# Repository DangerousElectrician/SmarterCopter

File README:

better brains for a syma 107 toy helicopter

Stuff to fix:
Holes are spaced back to front. Hole sizes are fine
U2 grounding pad covered by soldermask
Mousebites need to be sanded flat

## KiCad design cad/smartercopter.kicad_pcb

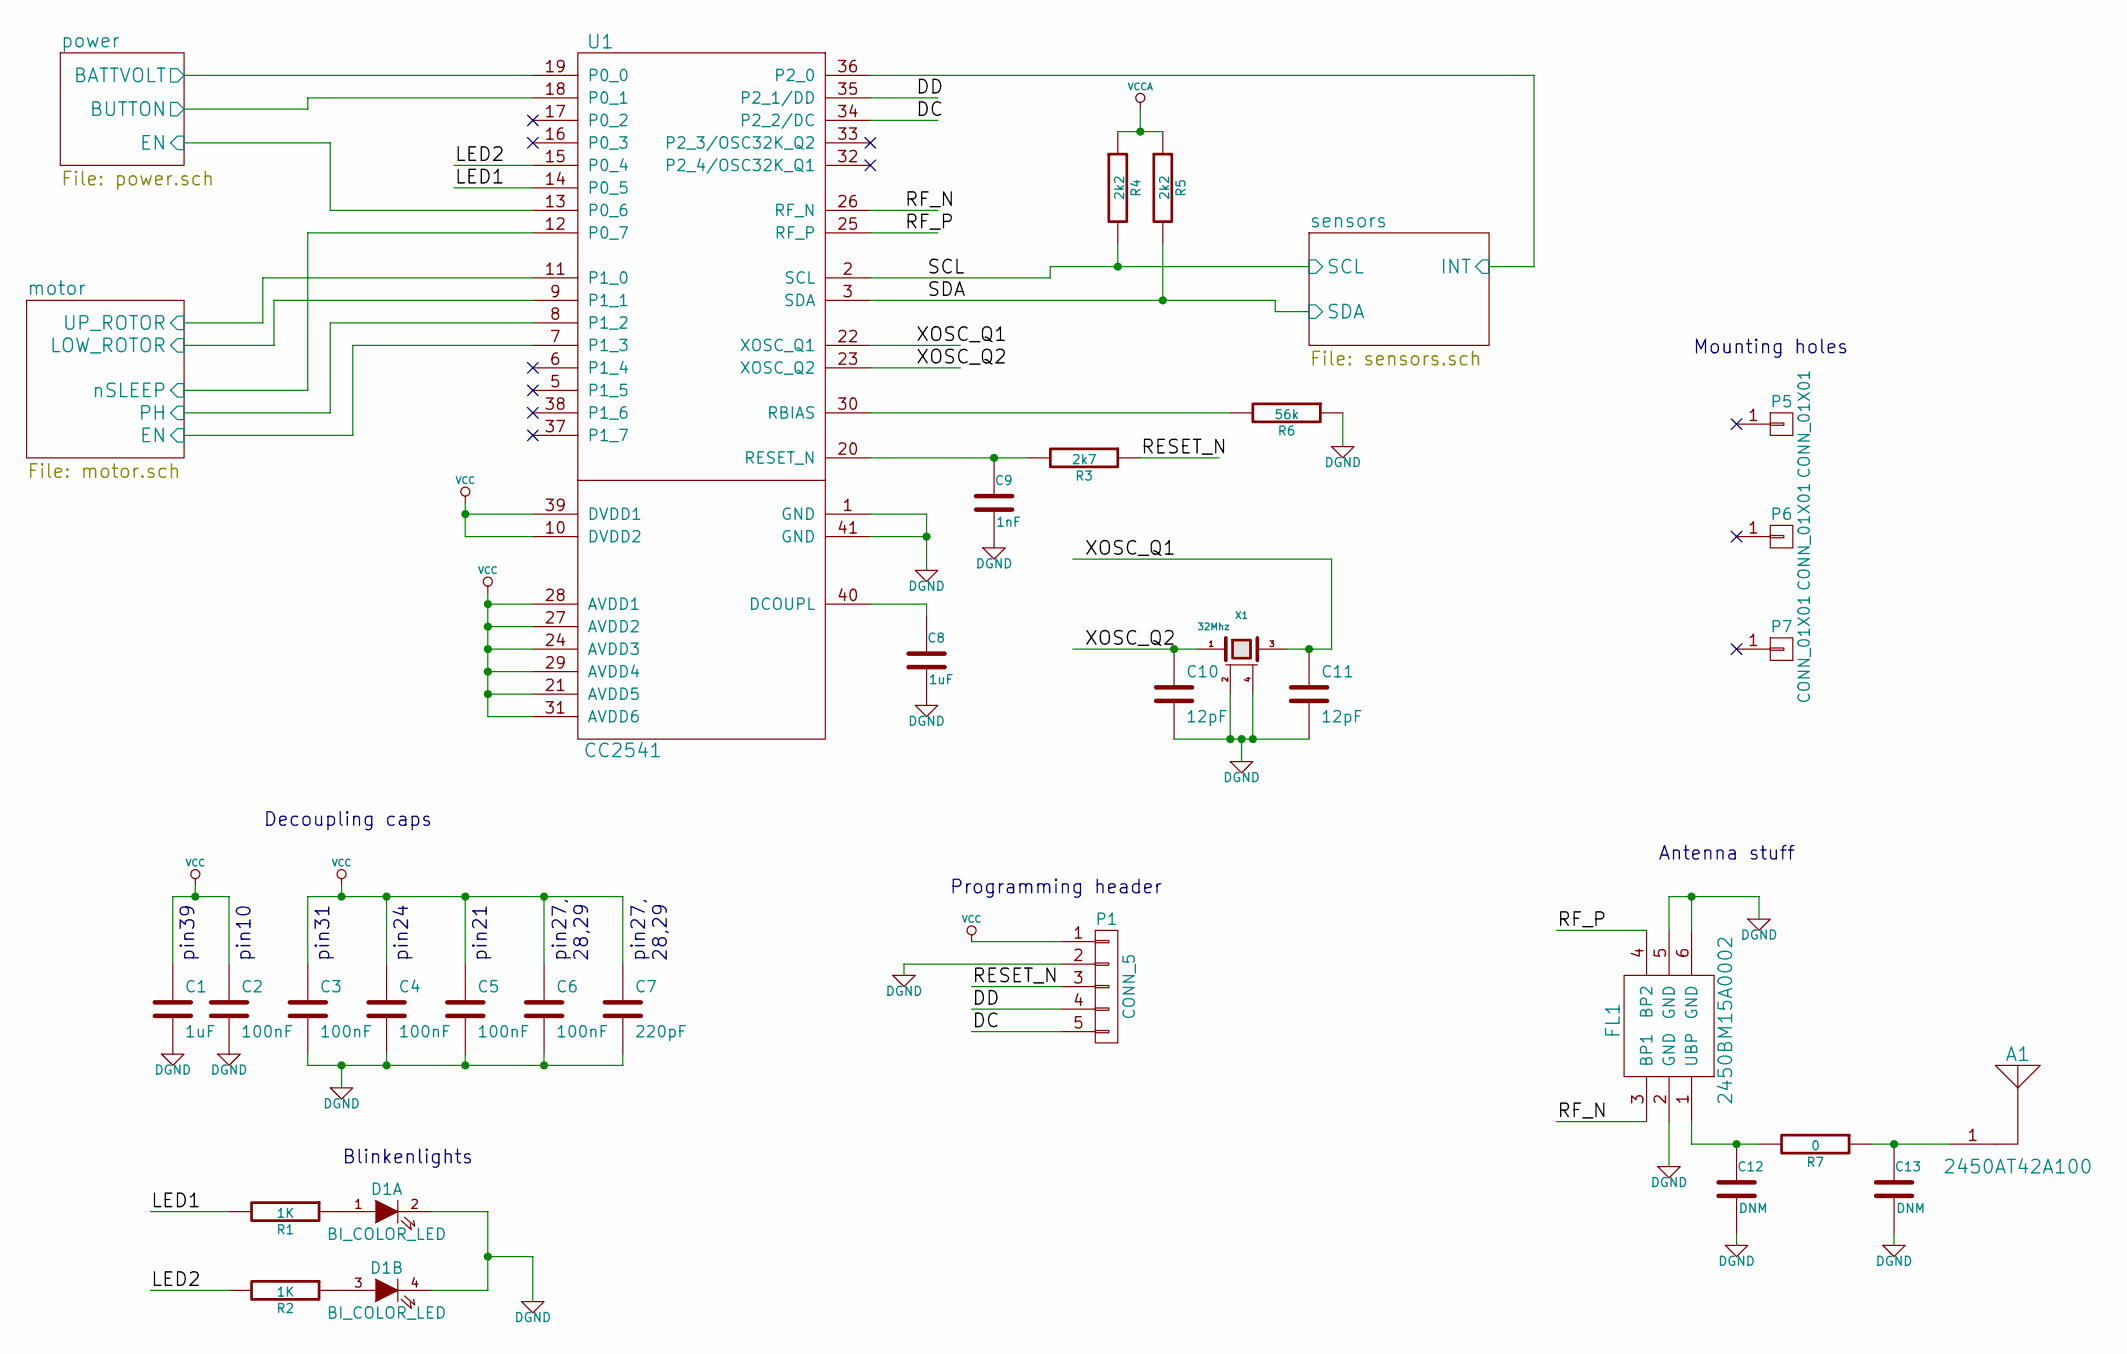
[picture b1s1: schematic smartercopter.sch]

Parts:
A1: 2450AT42A100; MPN 2450AT42A100
C1: 1uF; C_0402; MPN GRM155R60J105KE19D
C2: 100nF; C_0402; MPN LMK105BJ104KV-F
C3, C4, C5, C6: 100nF; C_0402
C7: 220pF; C_0402; MPN CC0402KRX7R9BB221
C8: 1uF; C_0402
C9: 1nF; C_0402; MPN GRM155R71H102KA01D
C10: 12pF; C_0201; MPN 02013A120JAT2A
C11: 12pF; C_0201
C12, C13: DNM; C_0402
D1: BI_COLOR_LED; APTB1612ESGC-F01; MPN APTB1612ESGC-F01
FL1: 2450BM15A0002; MPN 2450BM15A0002
P1: CONN_5; pin_array_1x05
P5, P6, P7: CONN_01X01; MountingHole_3mm
R1: 1K; R_0402; MPN 1-1622826-8
R2: 1K; R_0402
R3: 2k7; R_0402; MPN RMCF0402JT2K70
R4, R5: 2k2; R_0402
R6: 56k; R_0402; MPN MCR01MRTF5602
R7: 0; R_0402
U1: CC2541; VQFN-40; MPN CC2541F256RHAR
X1: 32Mhz; 4-SMD; MPN FA-128 32.0000MF20X-K3

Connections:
/DC: P1.5, U1.34 (P2_2/DC)
/DD: P1.4, U1.35 (P2_1/DD)
/LED1: R1.2, U1.14 (P0_5)
/LED2: R2.2, U1.15 (P0_4)
/RESET_N: P1.3, R3.1
/RF_N: FL1.3 (BP1), U1.26 (RF_N)
/RF_P: FL1.4 (BP2), U1.25 (RF_P)
/XOSC_Q1: C11.1, U1.22 (XOSC_Q1), X1.3
/XOSC_Q2: C10.1, U1.23 (XOSC_Q2), X1.1
/motor/EN: U1.7 (P1_3); also elsewhere on the board
/motor/LOW_ROTOR: U1.9 (P1_1); also elsewhere on the board
/motor/PH: U1.8 (P1_2); also elsewhere on the board
/motor/UP_ROTOR: U1.11 (P1_0); also elsewhere on the board
/motor/nSLEEP: U1.12 (P0_7); also elsewhere on the board
/power/BATTVOLT: U1.19 (P0_0); also elsewhere on the board
/power/BUTTON: U1.18 (P0_1); also elsewhere on the board
/power/EN: U1.13 (P0_6); also elsewhere on the board
/sensors/INT: U1.36 (P2_0); also elsewhere on the board
/sensors/SCL: R4.2, U1.2 (SCL); also elsewhere on the board
/sensors/SDA: R5.2, U1.3 (SDA); also elsewhere on the board
DGND: C1.2, C2.2, C3.2, C4.2, C5.2, C6.2, C7.2, C8.2, C9.2, C10.2, C11.2, C12.2, C13.2, D1.2 (K), D1.4 (K), FL1.2 (GND), FL1.5 (GND), FL1.6 (GND), P1.2, R6.1, U1.1 (GND), U1.41 (GND), X1.2 (GND), X1.4 (GND); also elsewhere on the board
unnamed: A1.1, C13.1, R7.1
unnamed: C8.1, U1.40 (DCOUPL)
unnamed: C9.1, R3.2, U1.20 (RESET_N)
unnamed: C12.1, FL1.1 (UBP), R7.2
unnamed: D1.1 (A), R1.1
unnamed: D1.3 (A), R2.1
unnamed: R6.2, U1.30 (RBIAS)
VCC: C1.1, C2.1, C3.1, C4.1, C5.1, C6.1, C7.1, P1.1, U1.10 (DVDD2), U1.21 (AVDD5), U1.24 (AVDD3), U1.27 (AVDD2), U1.28 (AVDD1), U1.29 (AVDD4), U1.31 (AVDD6), U1.39 (DVDD1); also elsewhere on the board
VCCA: R4.1, R5.1; also elsewhere on the board

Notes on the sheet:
pin39
pin10
pin31
pin24
pin21
pin27, 28,29
Blinkenlights
Antenna stuff
Programming header
Decoupling caps
Mounting holes

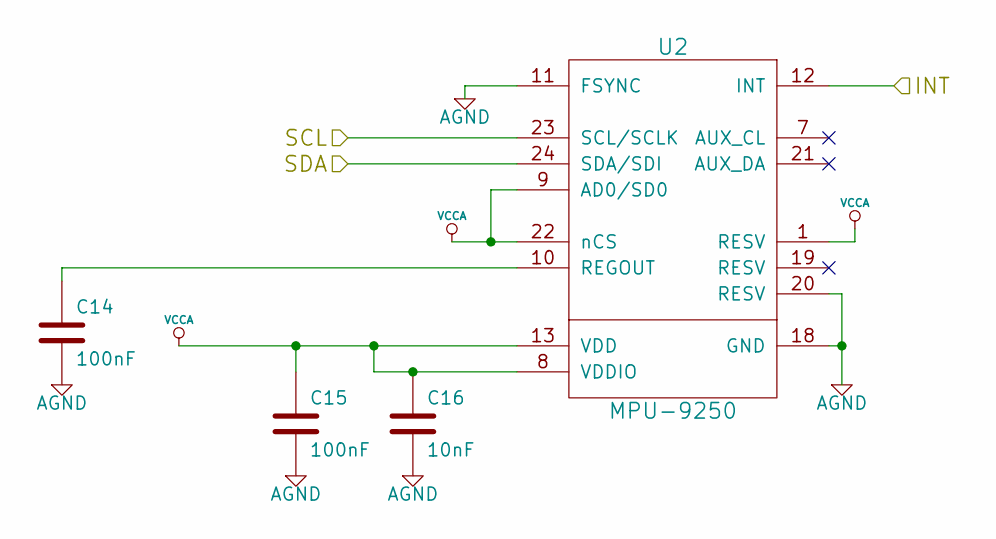
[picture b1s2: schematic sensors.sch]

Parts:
C14, C15: 100nF; C_0402
C16: 10nF; C_0402; MPN GRM155R71E103KA01D
U2: MPU-9250; QFN-28-1EP; MPN MPU-9250

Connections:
/sensors/INT: U2.12 (INT); also elsewhere on the board
/sensors/SCL: U2.23 (SCL/SCLK); also elsewhere on the board
/sensors/SDA: U2.24 (SDA/SDI); also elsewhere on the board
AGND: C14.2, C15.2, C16.2, U2.11 (FSYNC), U2.18 (GND), U2.20 (RESV); also elsewhere on the board
unnamed: C14.1, U2.10 (REGOUT)
VCCA: C15.1, C16.1, U2.1 (RESV), U2.8 (VDDIO), U2.9 (AD0/SD0), U2.13 (VDD), U2.22 (nCS); also elsewhere on the board

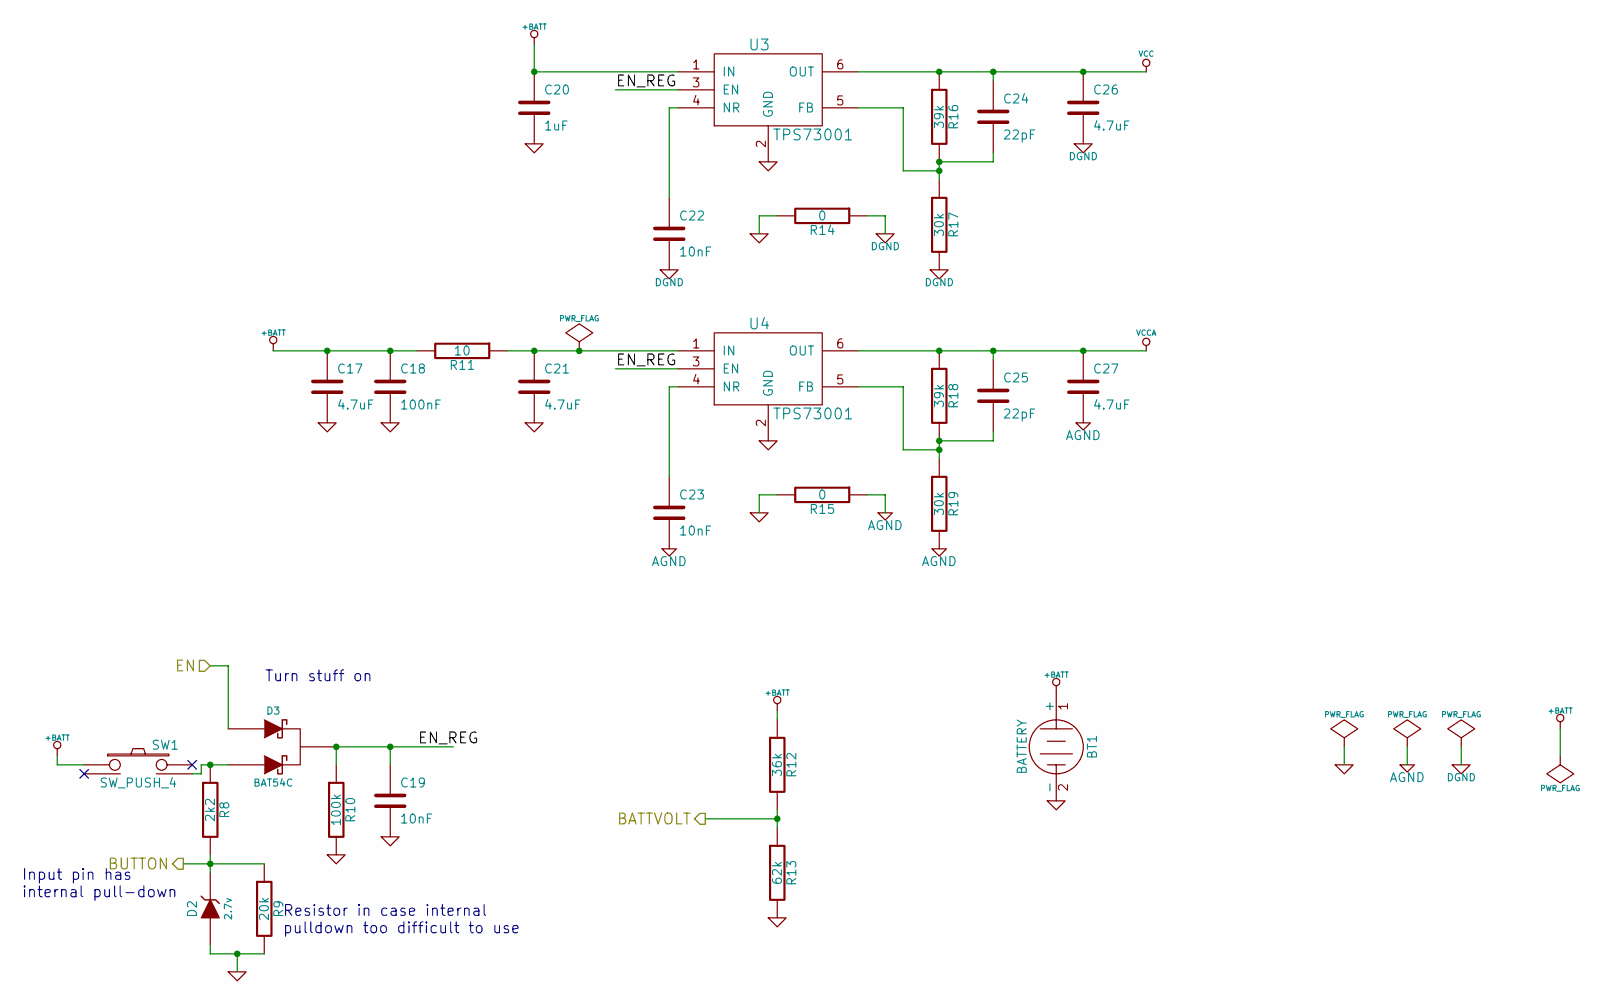
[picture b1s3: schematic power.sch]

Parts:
BT1: BATTERY; Pin_Header_Straight_1x02
C17, C21, C27: 4.7uF; C_0603
C18: 100nF; C_0402
C19, C22, C23: 10nF; C_0402
C20: 1uF; C_0402
C24: 22pF; C_0402; MPN CL05C220JB5NNNC
C25: 22pF; C_0402
C26: 4.7uF; C_0603; MPN CL10B475KQ8NQNC
D2: 2.7v; SOD-323; MPN MM3Z2V7T1G
D3: BAT54C; Diode_SOT23
R8: 2k2; R_0402; MPN RMCF0402JT2K20
R9: 20k; R_0402; MPN MCR01MRTF2002
R10: 100k; R_0402; MPN MCR01MRTF1003
R11: 10; R_0402; MPN MCR01MRTF10R0
R12: 36k; R_0402; MPN MCR01MRTF3602
R13: 62k; R_0402; MPN MCR01MRTJ623
R14: 0; R_0402; MPN RC1005J000CS
R15: 0; R_0402
R16: 39k; R_0402; MPN RC1005J393CS
R17: 30k; R_0402; MPN RC1005J303CS
R18: 39k; R_0402
R19: 30k; R_0402
SW1: SW_PUSH_4; PTS840GMSMTRLFS; MPN PTS840 GM SMTR LFS
U3: TPS73001; SOT-23-6; MPN TPS73001DBVR
U4: TPS73001; SOT-23-6

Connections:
+BATT: BT1.1 (+), C17.1, C18.1, C20.1, R11.2, R12.1, SW1.1, U3.1 (IN); also elsewhere on the board
/power/BATTVOLT: R12.2, R13.1; also elsewhere on the board
/power/BUTTON: D2.2 (K), R8.2, R9.1; also elsewhere on the board
/power/EN: D3.1; also elsewhere on the board
/power/EN_REG: C19.1, D3.3, R10.1, U3.3 (EN), U4.3 (EN)
AGND: C23.2, C27.2, R15.1, R19.2; also elsewhere on the board
DGND: C22.2, C26.2, R14.1, R17.2; also elsewhere on the board
GND: BT1.2 (-), C17.2, C18.2, C19.2, C20.2, C21.2, D2.1 (A), R9.2, R10.2, R13.2, R14.2, R15.2, U3.2 (GND), U4.2 (GND); also elsewhere on the board
unnamed: C21.1, R11.1, U4.1 (IN)
unnamed: C22.1, U3.4 (NR)
unnamed: C23.1, U4.4 (NR)
unnamed: C24.2, R16.2, R17.1, U3.5 (FB)
unnamed: C25.2, R18.2, R19.1, U4.5 (FB)
unnamed: D3.2, R8.1, SW1.4
VCC: C24.1, C26.1, R16.1, U3.6 (OUT); also elsewhere on the board
VCCA: C25.1, C27.1, R18.1, U4.6 (OUT); also elsewhere on the board

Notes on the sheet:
Input pin has internal pull-down
Resistor in case internal pulldown too difficult to use
Turn stuff on

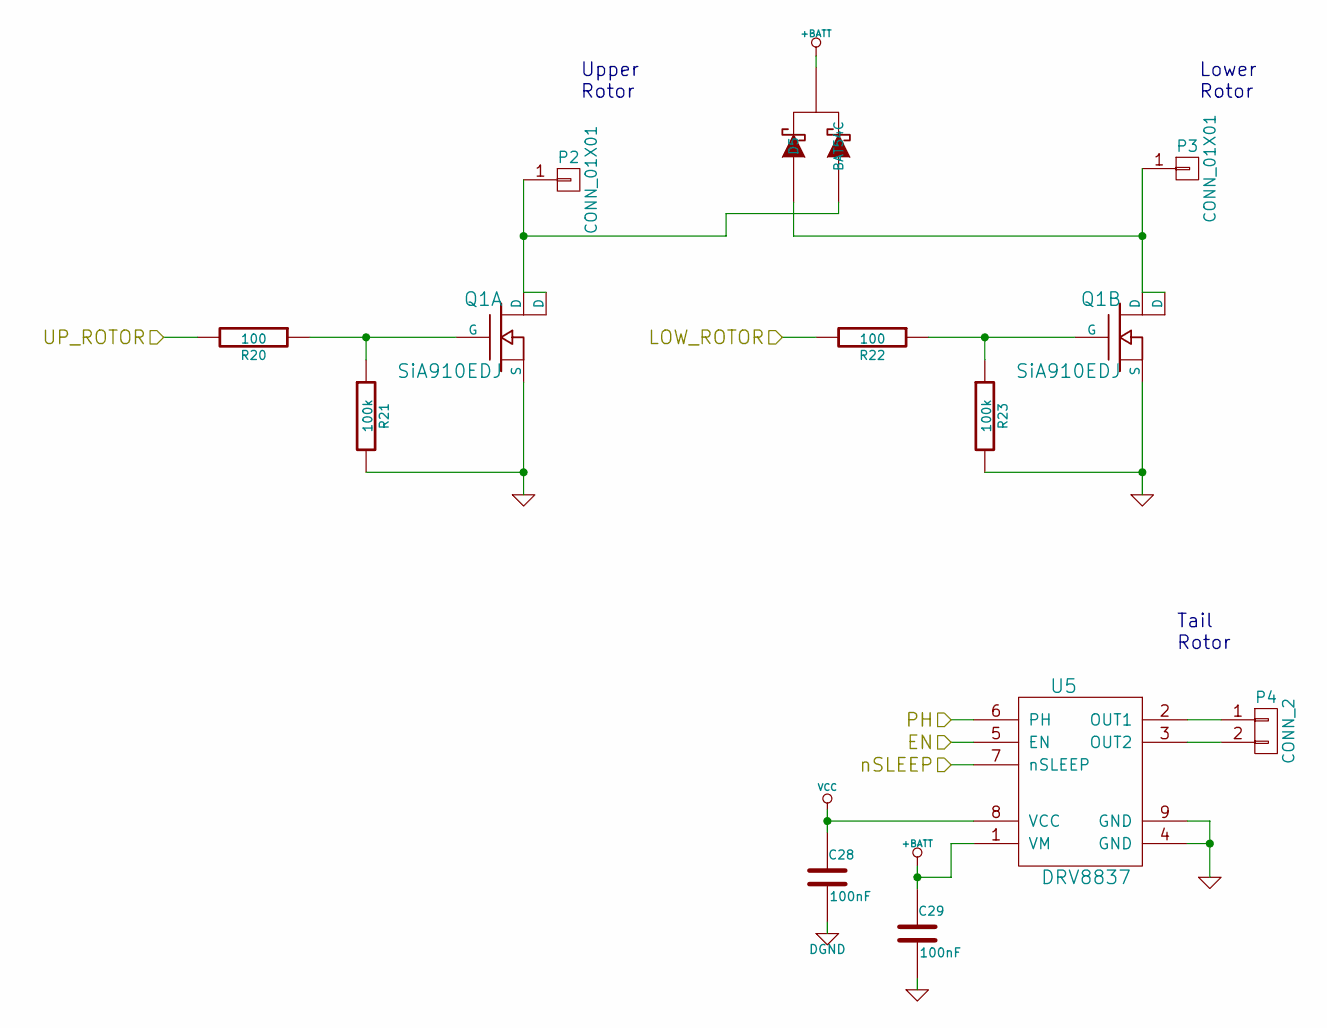
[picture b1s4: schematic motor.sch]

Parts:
C28, C29: 100nF; C_0402
D5: BAT54C; Diode_SOT23; MPN BAT54C
P2, P3: CONN_01X01; Pin_Header_Straight_1x01
P4: CONN_2; Pin_Header_Straight_1x02
Q1: SiA910EDJ; SC-70-6L; MPN SIA910EDJ-T1-GE3
R20: 100; R_0402; MPN MCR01MRTF1000
R21, R23: 100k; R_0402
R22: 100; R_0402
U5: DRV8837; WSON-8-1EP; MPN DRV8837DSGR

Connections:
+BATT: C29.1, D5.3, U5.1 (VM); also elsewhere on the board
/motor/EN: U5.5 (EN); also elsewhere on the board
/motor/LOW_ROTOR: R22.2; also elsewhere on the board
/motor/PH: U5.6 (PH); also elsewhere on the board
/motor/UP_ROTOR: R20.2; also elsewhere on the board
/motor/nSLEEP: U5.7 (nSLEEP); also elsewhere on the board
DGND: C28.2; also elsewhere on the board
GND: C29.2, Q1.1 (S), Q1.4 (S), R21.2, R23.2, U5.4 (GND), U5.9 (GND); also elsewhere on the board
unnamed: D5.1, P3.1, Q1.3 (D), Q1.D2 (D)
unnamed: D5.2, P2.1, Q1.6 (D), Q1.D1 (D)
unnamed: P4.1, U5.2 (OUT1)
unnamed: P4.2, U5.3 (OUT2)
unnamed: Q1.2 (G), R20.1, R21.1
unnamed: Q1.5 (G), R22.1, R23.1
VCC: C28.1, U5.8 (VCC); also elsewhere on the board

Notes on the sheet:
Upper Rotor
Lower Rotor
Tail Rotor

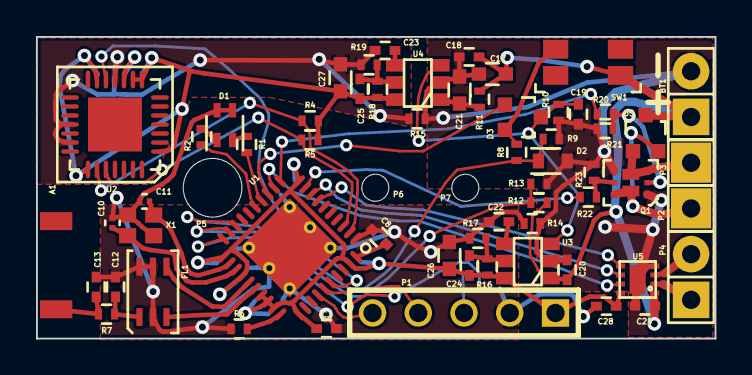
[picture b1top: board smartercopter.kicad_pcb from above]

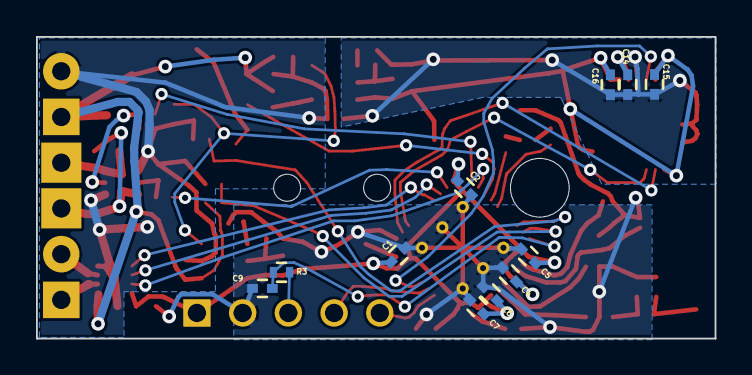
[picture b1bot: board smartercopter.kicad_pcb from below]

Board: 2 copper layers, 37.7 x 16.8 mm, 74 parts (11 on the bottom side), 47 nets.

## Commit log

2014-12-07 init commit
2014-12-08 added more sensor and processor considerations
2014-12-09 more details to microprocessor selection
2014-12-09 more stuff about sensors
2014-12-09 considering another sensor
2014-12-10 added requirements at top and a bit more information on sensors and motor drive
2014-12-10 more stuff on todo list
2014-12-10 figured out power requirements of CC2541 and MPU9250
2014-12-10 added some voltage regulator details
2014-12-11 added soft power switch pins to pin list
2014-12-11 added stuff about flyback diodes
2014-12-12 added soft power switch information
2014-12-14 changed voltage regulator
2014-12-17 schematics and datasheets
2014-12-17 added values to crystal load caps
2014-12-17 passed erc
2014-12-17 cleaned up a bit
2014-12-17 added .gitignore
2014-12-17 stuff
2014-12-18 something required to generate a BOM. not quite sure what it does
2014-12-18 auto generated xml file that does something
2014-12-18 did stuff here, not exactly sure what
2014-12-18 added more stuff to bom
2014-12-18 selecting parts for the little passives
2014-12-19 whole bunch of stuff
2014-12-19 more stuff
2014-12-20 reshuffled libraries
2014-12-20 updated libraries on .net file
2014-12-20 updated BOM
2014-12-21 crystal datasheet
2014-12-21 pcb file
2014-12-21 added more footprint stuff
2014-12-22 bunch more footprints assigned
2014-12-22 everything has a footprint
2014-12-22 all components spread out on sheet
2014-12-22 found out decoupling caps are not connected in the net
2014-12-23 arranged stuff into smaller groups
2014-12-23 components packed closer
2014-12-23 board outline
2014-12-23 added board outline
2014-12-23 made motor pads single to save space
2014-12-24 packed most of the components on to board
2014-12-24 everything on board
2014-12-24 routing first, then placing
2014-12-24 routed voltage regulators
2014-12-25 routed some stuff
2014-12-26 stuff on board with a bit of routing
2014-12-26 stuff on board
2014-12-27 progress check in
2014-12-27 freerouting stuff
2014-12-28 more routing
2014-12-30 components placed again
2014-12-30 freerouting files
2015-01-01 routing almost done
2015-01-01 everything routed
2015-01-02 everything routed for sure this time
2015-01-02 no drc errors
2015-01-02 added some ground planes
2015-01-04 added readme
2015-01-05 more power planes
2015-01-11 double checking qfn-40 footprint
2015-01-15 changed cc2451 footprint center pad
2015-01-17 all routed
2015-01-18 added ground planes
2015-01-18 changed ground plane clearences
2015-01-23 example script from the manual
2015-02-02 don't write anything
2015-02-05 figured out how to change text dimensions from script
2015-02-05 shrank all component references
2015-02-05 renamed script
2015-02-05 shrank all the silkscreen references
2015-02-05 git wants me to delete this in a weird way
2015-02-06 moved references around
2015-02-06 renamed files
2015-02-07 increased soldermask clearance from 0 to 3mil
2015-02-07 rerouted traces near the edge
2015-02-07 changed some 3d footprints
2015-02-07 generated gerbers
2015-02-07 ignore zipped gerbers
2015-02-25 stuff that should be fixed
2015-03-05 regenerate bom, nothing changed really
2015-04-01 hid all value text
2015-04-02 created assembly reference materials and organized directory a little
